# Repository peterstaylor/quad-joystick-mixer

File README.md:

# quad-joystick-mixer
This is a README for the quadrophonic joystick mixer design

# Hardware
## IO Summary: 
### Digital Interface: 
We have two I2C interfaces which is more than we techincally need for this board, but is how many we'll need if we go to 8 inputs to to the mixer. Each input requires two digital pots, so that's 16 total digital pots and each i2c interface can only support up to 8 digital pots

- I2C 0 controls the digital pots for input channel 1
- I2C 1 controls the digital pots for input channel 2

### Outputs: 
I included LED indicators to help in development and for general app use as needed: 
- Red LED Indicator = Teensy Digital Output 2
- Blue LED Indicator = Teensy Digital Output 3

### Inputs: 
#### Buttons: 
There are three buttons that can be used however needed. Three might be more than we actually need, but I had spare I/O
- Button 1 = Teensy Digital Input 7
- Button 2 = Teensy Digital Input 8
- Button 3 = Teensy Digital Input 7

I've also bought out the PROGRAM and POWER pins on the Teensy to buttons. I don't think we need these, but I wasn't sure so I included them in this first revision. 

#### Analaog Inputs: 
- Encoder channel selection input = Teensy Analog Input 14
    - I used an analog input for channel selection instead of something digital so I could save I/O on the micro. If this interface is flaky we can switch to digital for the next spin of the board
- Joystick AB Control Input = Teensy Analog Input 15
- Joystick CD Control Input = Teensy Analog Input 20 

## V1 to V2 Change Log: 
- [] Use attenuator as front-end gain control instead of amplifier feedback gain
- [] Add additional filtering to VCC and VDD rails 
- [] upgrade to lower noise op-amps
- [] don't route the dang i2c nets over a cut in the ground plane!!! 
- [] Add analog filtering and buffering to the input path from the encoder to smoothe out readings
- [] revisit output gain and mixing
- [] Add six more analog inputs for a total of 8 inputs 
- [] Perform electromechanical integration work once the design is working

# Firmware
## Teensy 
- Link to Teensy tutorial: https://www.pjrc.com/teensy/tutorial.html
- Link to how to set up a portable install of the Arduino IDE: https://docs.arduino.cc/software/ide-v1/tutorials/PortableIDE/
    - I had to set up a portable install to get all the teensy libraries to install correctly and compile the code

## Board Level Test (BLT) Code
This code is written to exercise the I/O on the system in a simple way just to verify the hardware

### Major Board Level Test Functions: 
- checkBLTTransition(): 
    - This function looks for the user to press down button 1 for a certain amount of time and then puts the board in BLT mode
- flash(): 
    - flashes both LEDs the desired number of times
    - input argument is an int setting the number of flashes
- analogReadToChannelCount: 
    - input argument is an int return from reading the encoder ADC channel
    - output is the channel of the mixer 1 through 8
    - use this function to determine what channel the user is trying to control
- binaryLED: 
    - input is int of channel count 
    - i used this for BLT to verify i was iterating through the channels visually
- calibrateJoystick: 
    - I'm not using this function right now but will probably be useful for application as I've already seen that there are inconsistencies between the two joysticks I have

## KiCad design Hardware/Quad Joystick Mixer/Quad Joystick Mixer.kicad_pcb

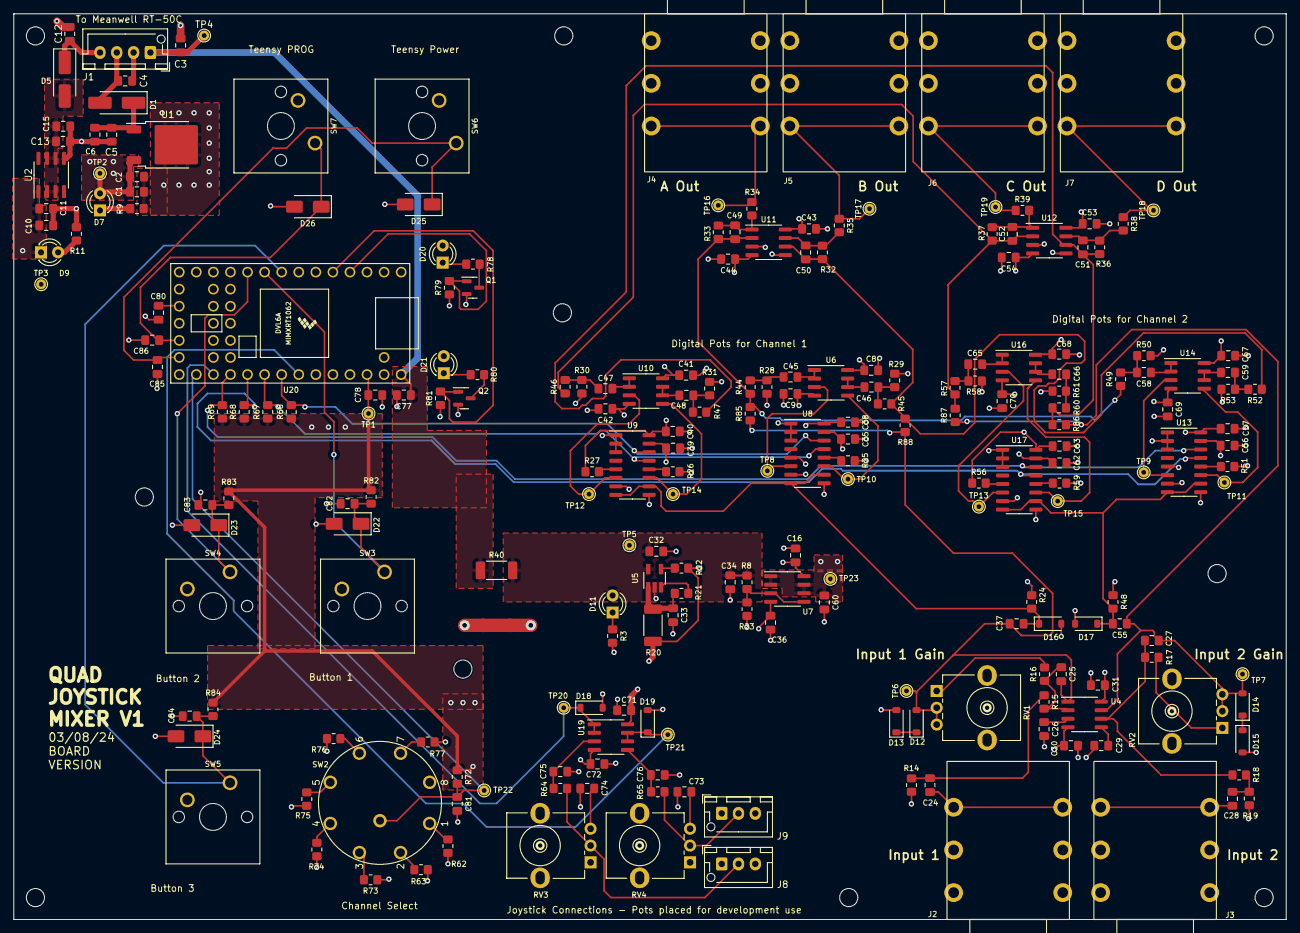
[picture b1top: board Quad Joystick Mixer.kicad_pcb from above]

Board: 4 copper layers, 189.3 x 134.8 mm, 228 parts (0 on the bottom side), 106 nets.

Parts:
C1, C10, C26, C29, C75, C76: 10uF; C_0805_2012Metric_Pad1.18x1.45mm_HandSolder
C2, C5, C8, C9, C11, C13, C16, C30, C31, C34, C35, C36, C38, C39, C40, C41, C42, C43, C44, C53, C54, C56, C57, C60, C62, C63, C67, C68, C69, C70, C71, C72, C73, C74, C77, C78, C80, C81, C82, C83, C84, C85, C86: 0.1uF; C_0805_2012Metric_Pad1.18x1.45mm_HandSolder
C3, C4, C6, C12, C15, C24, C28, C32, C33, C37, C45, C46, C47, C48, C55, C58, C59, C65, C66: 1uF; C_0805_2012Metric_Pad1.18x1.45mm_HandSolder
C25, C27: 10pF; C_0805_2012Metric_Pad1.18x1.45mm_HandSolder
C49, C50, C51, C52: 330pF; C_0805_2012Metric_Pad1.18x1.45mm_HandSolder
D1, D5: B350; D_SMA_Handsoldering
D7, D9, D11, D20, D21: LED; LED_D3.0mm_FlatTop
D12, D13, D14, D15: MMSZ5222BT1G; D_SOD-123
D16, D17: BZT52C4V7-13-F; D_SOD-123
D18, D19: DDZ9684-7; D_SOD-123
D22, D23, D24, D25, D26: SMAJ5.0A; D_SMA
J1: XH-B4B-XH; JST_XH_B4B-XH-AM_1x04_P2.50mm_Vertical
J2, J3, J4, J5, J6, J7: NMJ6HCD
J8, J9: XH-A; JST_XH_B3B-XH-AM_1x03_P2.50mm_Vertical
NT1: NetTie_2; NetTie-2_SMD_Pad2.0mm
Q1, Q2: 2N7002; SOT-23
R3: 3k; R_0805_2012Metric_Pad1.20x1.40mm_HandSolder
R8, R23, R32, R33, R36, R37: 20k; R_0805_2012Metric_Pad1.20x1.40mm_HandSolder
R9, R11, R21, R22, R25, R26, R27, R44, R45, R46, R47, R49, R51, R52, R56, R57, R59, R60, R72, R74, R79, R81, R82, R83, R84: 10k; R_0805_2012Metric_Pad1.20x1.40mm_HandSolder
R14, R19, R24, R28, R29, R30, R31, R48, R50, R53, R58, R61: 100k; R_0805_2012Metric_Pad1.20x1.40mm_HandSolder
R15, R18, R66, R67, R68, R69: 4.7k; R_0805_2012Metric_Pad1.20x1.40mm_HandSolder
R16, R17: 470; R_0805_2012Metric_Pad1.20x1.40mm_HandSolder
R20: 4.7R; R_2010_5025Metric_Pad1.40x2.65mm_HandSolder
R34, R35, R38, R39: 1k; R_0805_2012Metric_Pad1.20x1.40mm_HandSolder
R40: DNA; R_2010_5025Metric_Pad1.40x2.65mm_HandSolder
R62: 1.43k; R_0805_2012Metric_Pad1.20x1.40mm_HandSolder
R63: 3.32k; R_0805_2012Metric_Pad1.20x1.40mm_HandSolder
R64, R65: 100; R_0805_2012Metric_Pad1.20x1.40mm_HandSolder
R73: 6.04k; R_0805_2012Metric_Pad1.20x1.40mm_HandSolder
R75: 16.5k; R_0805_2012Metric_Pad1.20x1.40mm_HandSolder
R76: 30.1k; R_0805_2012Metric_Pad1.20x1.40mm_HandSolder
R77: 71.5k; R_0805_2012Metric_Pad1.20x1.40mm_HandSolder
R78, R80: 200; R_0805_2012Metric_Pad1.20x1.40mm_HandSolder
R85, R86, R87, R88: DNA; R_0805_2012Metric_Pad1.20x1.40mm_HandSolder
RV1, RV2: 500kA; StomboxParts_9MM
RV3, RV4: 10k-B; StomboxParts_9MM
SW2: Stompbox 1P8T Rotary
SW3, SW4, SW5, SW6, SW7: Cherry MX; SW_Cherry_MX_1.00u_PCB
TP1, TP2, TP3, TP4, TP5, TP6, TP7, TP8, TP9, TP10, TP11, TP12, TP13, TP14, TP15, TP16, TP17, TP18, TP19, TP20, TP21, TP22, TP23: TestPoint; TestPoint_THTPad_D1.5mm_Drill0.7mm
U1: L78M12ACDT-TR; TO-252-2
U2: MC79L12ABDG; SOIC-8_3.9x4.9mm_P1.27mm
U4, U6, U7, U10, U11, U12, U14, U16, U19: TL072; SOIC-8_3.9x4.9mm_P1.27mm
U5: MCP1755T-5002E/OT; SOT-23-5_HandSoldering
U8, U9, U13, U17: DS1881Z-050+; SOIC-16_3.9x9.9mm_P1.27mm
U20: Teensy4.0; Teensy40

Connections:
+3.3V: C38.1, C40.1, C57.1, C63.1, C73.1, C74.1, C78.1, C80.1, D20.2 (A), D21.2 (A), J8.1, J9.1, R27.1, R56.1, R66.1, R67.1, R68.1, R69.1, R72.1, R82.2, R83.2, R84.2, RV3.3, RV4.3, TP1.1, U8.16 (VDD), U9.16 (VDD), U13.16 (VDD), U17.16 (VDD), U20.16 (3V3), U20.31 (3V3)
+5V: C3.1, C77.1, J1.1, R40.1, TP4.1, U20.33 (VIN)
+12V: C1.1, C2.1, C8.1, C16.1, C31.1, C41.1, C43.1, C53.1, C67.1, C68.1, C71.1, D7.2 (A), R20.2, R22.1, TP2.1, U1.3 (VO), U4.8 (V+), U6.8 (V+), U7.8 (V+), U10.8 (V+), U11.8 (V+), U12.8 (V+), U14.8 (V+), U16.8 (V+), U19.8 (V+)
+15V: C4.1, D1.2 (A), J1.3
-12V: C9.1, C10.1, C11.1, C30.1, C36.1, C42.1, C44.1, C54.1, C69.1, C70.1, C72.1, D9.1 (K), TP3.1, U2.1 (VOUT), U4.4 (V-), U6.4 (V-), U7.4 (V-), U10.4 (V-), U11.4 (V-), U12.4 (V-), U14.4 (V-), U16.4 (V-), U19.4 (V-)
-15V: C12.1, D5.1 (K), J1.4
/Audio Input/Channel1_Input: C25.2, C37.1, D12.2 (A), R85.1, R88.1, RV1.2, RV1.3, TP6.1, U4.1
/Audio Input/Channel2_Input: C27.2, C55.1, D14.2 (A), R86.1, R87.1, RV2.2, RV2.3, TP7.1, U4.7
/Audio Output/A: C49.1, R33.2, R44.1, R49.1, R85.2, U11.2 (-)
/Audio Output/B: C50.1, R32.2, R45.1, R52.1, R88.2, U11.6 (-)
/Audio Output/C: C52.1, R37.2, R46.1, R57.1, R87.2, U12.2 (-)
/Audio Output/D: C51.1, R36.2, R47.1, R60.1, R86.2, U12.6 (-)
/SCL0: R66.2, U8.14 (SCL), U9.14 (SCL), U20.26 (19_A5_SCL0)
/SCL1: R69.2, U13.14 (SCL), U17.14 (SCL), U20.23 (16_A2_RX4_SCL1)
/SDA0: R67.2, U8.13 (SDA), U9.13 (SDA), U20.25 (18_A4_SDA0)
/SDA1: R68.2, U13.13 (SDA), U17.13 (SDA), U20.24 (17_A3_TX4_SDA1)
/Teensy/AB_Control: D18.1 (K), TP20.1, U19.1, U19.2 (-), U20.22 (15_A1_RX3_SPDIF_IN)
/Teensy/Button_1: C82.1, D22.1 (A1), R82.1, SW3.1 (A), U20.9 (7_RX2_OUT1A)
/Teensy/Button_2: C83.1, D23.1 (A1), R83.1, SW4.1 (A), U20.10 (8_TX2_IN1)
/Teensy/Button_3: C84.1, D24.1 (A1), R84.1, SW5.1 (A), U20.8 (6_OUT1D)
/Teensy/CD_Control: D19.1 (K), TP21.1, U19.6 (-), U19.7, U20.27 (20_A6_TX5_LRCLK1)
/Teensy/Channel Selection: C81.1, R72.2, SW2.9, TP22.1, U20.21 (14_A0_TX3_SPDIF_OUT)
/Teensy/LED_1: Q1.1 (G), R79.2, U20.4 (2_OUT2)
/Teensy/LED_2: Q2.1 (G), R81.2, U20.5 (3_LRCLK2)
/Teensy/POWER: C85.1, D25.1 (A1), SW6.1 (A), U20.19 (ON_OFF)
/Teensy/PROGRAM: C86.1, D26.1 (A1), SW7.1 (A), U20.18 (PROGRAM)
Earth: C1.2, C2.2, C3.2, C4.2, C5.2, C6.2, C10.2, C11.2, C12.2, C13.2, C15.2, C71.2, C72.2, C73.2, C74.2, C75.2, C76.2, C77.2, C78.2, C80.2, C81.2, C82.2, C83.2, C84.2, C85.2, C86.2, D18.2 (A), D19.2 (A), D22.2 (A2), D23.2 (A2), D24.2 (A2), D25.2 (A2), D26.2 (A2), J1.2, J8.3, J9.3, NT1.1, Q1.2 (S), Q2.2 (S), R9.2, R11.2, R62.2, R63.2, R73.2, R74.2, R75.2, R76.2, R77.2, R79.1, R81.1, RV3.1, RV4.1, SW3.2 (B), SW4.2 (B), SW5.2 (B), SW6.2 (B), SW7.2 (B), U1.2 (GND), U2.5 (GND), U20.1 (GND), U20.17 (GND), U20.32 (GND)
GND: C8.2, C9.2, C16.2, C26.2, C29.2, C30.2, C31.2, C32.2, C33.2, C34.2, C35.2, C36.2, C38.2, C39.2, C40.2, C41.2, C42.2, C43.2, C44.2, C53.2, C54.2, C56.2, C57.2, C60.2, C62.2, C63.2, C67.2, C68.2, C69.2, C70.2, D13.2 (A), D15.2 (A), D16.2 (A), D17.2 (A), J2.S, J2.SN, J3.S, J3.SN, J4.S, J4.SN, J5.S, J5.SN, J6.S, J6.SN, J7.S, J7.SN, NT1.2, R3.2, R14.2, R19.2, R23.2, R25.2, R26.2, R28.2, R29.2, R30.2, R31.2, R50.2, R51.2, R53.2, R58.2, R59.2, R61.2, U5.2 (GND), U8.1 (GND), U8.2 (A2), U8.3 (A1), U8.5 (A0), U9.1 (GND), U9.2 (A2), U9.3 (A1), U11.3 (+), U11.5 (+), U12.3 (+), U12.5 (+), U13.1 (GND), U13.2 (A2), U13.3 (A1), U13.5 (A0), U17.1 (GND), U17.2 (A2), U17.3 (A1)
unnamed: C24.1, J2.T, J2.TN
unnamed: C24.2, R14.1, R15.1
unnamed: C28.1, J3.T, J3.TN
unnamed: C28.2, R18.1, R19.1
unnamed: C45.2, R28.1, R44.2
unnamed: C46.2, R29.1, R45.2
unnamed: C47.2, R30.1, R46.2
unnamed: C48.2, R31.1, R47.2
unnamed: C49.2, R33.1, R34.2, U11.1
unnamed: C50.2, R32.1, R35.2, U11.7
unnamed: C51.2, R36.1, R38.2, U12.7
unnamed: C52.2, R37.1, R39.2, U12.1
unnamed: C58.2, R49.2, R50.1
unnamed: C59.2, R52.2, R53.1
unnamed: C65.2, R57.2, R58.1
unnamed: C66.2, R60.2, R61.1
unnamed: C5.1, C6.1, D1.1 (K), U1.1 (VI)
unnamed: C13.1, C15.1, D5.2 (A), U2.2 (VIN), U2.3 (VIN), U2.6 (VIN), U2.7 (VIN)
unnamed: D7.1 (K), R9.1
unnamed: D9.2 (A), R11.1
unnamed: D11.1 (K), R3.1
unnamed: D12.1 (K), D13.1 (K)
unnamed: D14.1 (K), D15.1 (K)
unnamed: C37.2, D16.1 (K), R24.2, U8.8 (H0), U8.10 (H1), U9.8 (H0), U9.10 (H1)
unnamed: C55.2, D17.1 (K), R48.2, U13.8 (H0), U13.10 (H1), U17.8 (H0), U17.10 (H1)
unnamed: D20.1 (K), R78.2
unnamed: D21.1 (K), R80.2
unnamed: J4.T, J4.TN, R34.1, TP16.1
unnamed: J5.T, J5.TN, R35.1, TP17.1
unnamed: J6.T, J6.TN, R39.1, TP19.1
unnamed: J7.T, J7.TN, R38.1, TP18.1
unnamed: J8.2, R64.1, RV3.2
unnamed: J9.2, R65.1, RV4.2
unnamed: Q1.3 (D), R78.1
unnamed: Q2.3 (D), R80.1
unnamed: R16.2, RV1.1
unnamed: R17.2, RV2.1
unnamed: R62.1, SW2.1
unnamed: R63.1, SW2.2
unnamed: R73.1, SW2.3
unnamed: R74.1, SW2.4
unnamed: R75.1, SW2.5
unnamed: R76.1, SW2.6
unnamed: R77.1, SW2.7
unnamed: C26.1, U4.3 (+)
unnamed: C25.1, R15.2, R16.1, U4.2 (-)
unnamed: C29.1, U4.5 (+)
unnamed: C27.1, R17.1, R18.2, U4.6 (-)
unnamed: R22.2, U5.4 (PGOOD)
unnamed: C33.1, R20.1, R21.1, U5.1 (VIN)
unnamed: R21.2, U5.3 (nSHDN)
unnamed: TP8.1, U6.3 (+), U8.6 (W0)
unnamed: C45.1, U6.1, U6.2 (-)
unnamed: TP10.1, U6.5 (+), U8.11 (W1)
unnamed: C46.1, U6.6 (-), U6.7
unnamed: R8.2, R23.1, U7.3 (+), U7.5 (+)
unnamed: R25.1, U8.12 (nCE)
unnamed: R27.2, U9.5 (A0)
unnamed: R26.1, U9.12 (nCE)
unnamed: TP12.1, U9.6 (W0), U10.3 (+)
unnamed: C47.1, U10.1, U10.2 (-)
unnamed: TP14.1, U9.11 (W1), U10.5 (+)
unnamed: C48.1, U10.6 (-), U10.7
unnamed: TP9.1, U13.6 (W0), U14.3 (+)
unnamed: TP11.1, U13.11 (W1), U14.5 (+)
unnamed: R51.1, U13.12 (nCE)
unnamed: C58.1, U14.1, U14.2 (-)
unnamed: C59.1, U14.6 (-), U14.7
unnamed: TP13.1, U16.3 (+), U17.6 (W0)
unnamed: C65.1, U16.1, U16.2 (-)
unnamed: TP15.1, U16.5 (+), U17.11 (W1)
unnamed: C66.1, U16.6 (-), U16.7
unnamed: R56.2, U17.5 (A0)
unnamed: R59.1, U17.12 (nCE)
unnamed: C75.1, R64.2, U19.3 (+)
unnamed: C76.1, R65.2, U19.5 (+)
VCC: C32.1, C34.1, C35.1, C39.1, C56.1, C62.1, D11.2 (A), R8.1, R40.2, TP5.1, U5.5 (VOUT), U8.15 (VCC), U9.15 (VCC), U13.15 (VCC), U17.15 (VCC)
VDD: C60.1, R24.1, R48.1, TP23.1, U7.1, U7.2 (-), U7.6 (-), U7.7, U8.7 (L0), U8.9 (L1), U9.7 (L0), U9.9 (L1), U13.7 (L0), U13.9 (L1), U17.7 (L0), U17.9 (L1)

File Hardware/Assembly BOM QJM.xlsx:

Reference | Qty | Value | Footprint
C1, C10, C26, C29, C75, C76 | 6 | 10uF | 0805
C2, C5, C8, C9, C11, C13, C16, C30, C31, C34-C36, C38-C44, C53, C54, C56, C57, 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 | 43 | 0.1uF | 0805
C25, C27 | 2 | 10pF | 0805
C3, C4, C6, C12, C15, C24, C28, C32, C33, C37, C45-C48, C55, C58, C59, C65, C66 | 19 | 1uF | 0805
C49-C52 | 4 | 330pF | 0805
D1, D5 | 2 | B350 | SMA
D12-D15 | 4 | MMSZ5222BT1G | SOD-123
D16, D17 | 2 | BZT52C4V7-13-F | SOD-123
D18, D19 | 2 | DDZ9684-7 | SOD-123
D22-D26 | 5 | SMAJ5.0A | SMA
D7, D9, D11, D20, D21 | 5 | LED | 3.0mm LED
J1 | 1 | XH-B4B-XH | JST-4
J2-J7 | 6 | NMJ6HCD | NMJ6HCD
J8, J9 | 2 | XH-A | JST-3
NT1 | 1 | NetTie_2 | Net tie
Q1, Q2 | 2 | 2N7002 | SOT-23
R14, R19, R24, R28-R31, R48, R50, R53, R58, R61 | 12 | 100k | 0805
R15, R18, R66-R69 | 6 | 4.7k | 0805
R16, R17 | 2 | 470R | 0805
R20 | 1 | 4.7R | 0805
R3 | 1 | 3k | 0805
R34, R35, R38, R39 | 4 | 1k | 0805
R40, R85-R88 | 5 | DNA | -- mixed values --
R62 | 1 | 1.43k | 0805
R63 | 1 | 3.32k | 0805
R64, R65 | 2 | 100R | 0805
R73 | 1 | 6.04k | 0805
R75 | 1 | 16.5k | 0805
R76 | 1 | 30.1k | 0805
R77 | 1 | 71.5k | 0805
R78, R80 | 2 | 200R | 0805
R8, R23, R32, R33, R36, R37 | 6 | 20k | 0805
R9, R11, R21, R22, R25-R27, R44-R47, R49, R51, R52, R56, R57, R59, R60, R72, R7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 | 25 | 10k | 0805
RV1, RV2 | 2 | 500kA | 9mm pot
RV3, RV4 | 2 | 10k-B | 9mm pot
Reference | Qty | Value | Footprint
SW2 | 1 | Stompbox 1P8T Rotary | 1p8t rotary
SW3-SW7 | 5 | Cherry MX | Cherry MX
TP1-TP23 | 23 | TestPoint | TP
U1 | 1 | L78M12ACDT-TR | TO-252-2
U2 | 1 | MC79L12ABDG | SOIC-8
U20 | 1 | Teensy4.0 | Teensy
U4, U6, U7, U10-U12, U14, U16, U19 | 9 | TL072 | SOIC-8
U5 | 1 | MCP1755T-5002E/OT | SOT-23-5
U8, U9, U13, U17 | 4 | DS1881Z-050+ | SOIC-16

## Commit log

2024-02-02 start on the power supply design
2024-02-12 workign on draft of PSU circuit--thinking about making it onto its own board
2024-02-12 progress on PSU layout
2024-02-13 clean up power supply schematic
2024-02-13 add image for reference to block diagram
2024-02-13 work on audio input circuit
2024-02-13 a few notes about changes
2024-02-13 add analog 5V rail
2024-02-13 more progress on schematic
2024-02-13 work through digital pot circuit
2024-02-13 working on finishing a draft of this dang schematic
2024-02-13 create joystick conditioning circuit
2024-02-14 progress on schematic
2024-02-14 add in rotary circuit and some docs
2024-02-14 finished first draft of the schematic
2024-02-14 ok the draft wasn't done but now i think it is
2024-02-15 clean up after review, working through BOM
2024-02-16 finish adding parts to the BOM
2024-02-19 work on placement and layout
2024-02-20 major layout progress
2024-02-20 more progress on layout
2024-02-20 more work no routing the board
2024-02-21 update layout
2024-02-21 three nets left to route
2024-02-21 work through DRC errors
2024-03-06 changed power supply design and everything re routed
2024-03-06 clean up DRC results
2024-06-07 add FW, updated README
2024-06-07 add more detail to readme about hardware/firmware integration
2024-06-10 finished basic I2C comms verification
2024-06-10 working on config values for digital pots
2024-06-10 fix pot variable ranges
2024-06-10 add output toggling code
2024-06-10 little bit of clean up and re-org
2024-06-10 add mechanical integration stuff
2024-06-11 cleanup, add slowpan function
2024-06-11 got code up and running to toggle digital pots
2024-07-04 BLT should be ready to go
2024-07-09 fix the LED bug
2024-08-02 add some stuff to the change log
2024-08-02 fix some typos in the readme
2024-08-02 add a picture of the assembled V1 board
